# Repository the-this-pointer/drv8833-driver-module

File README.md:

### DRV8833 Stepper Motor Module

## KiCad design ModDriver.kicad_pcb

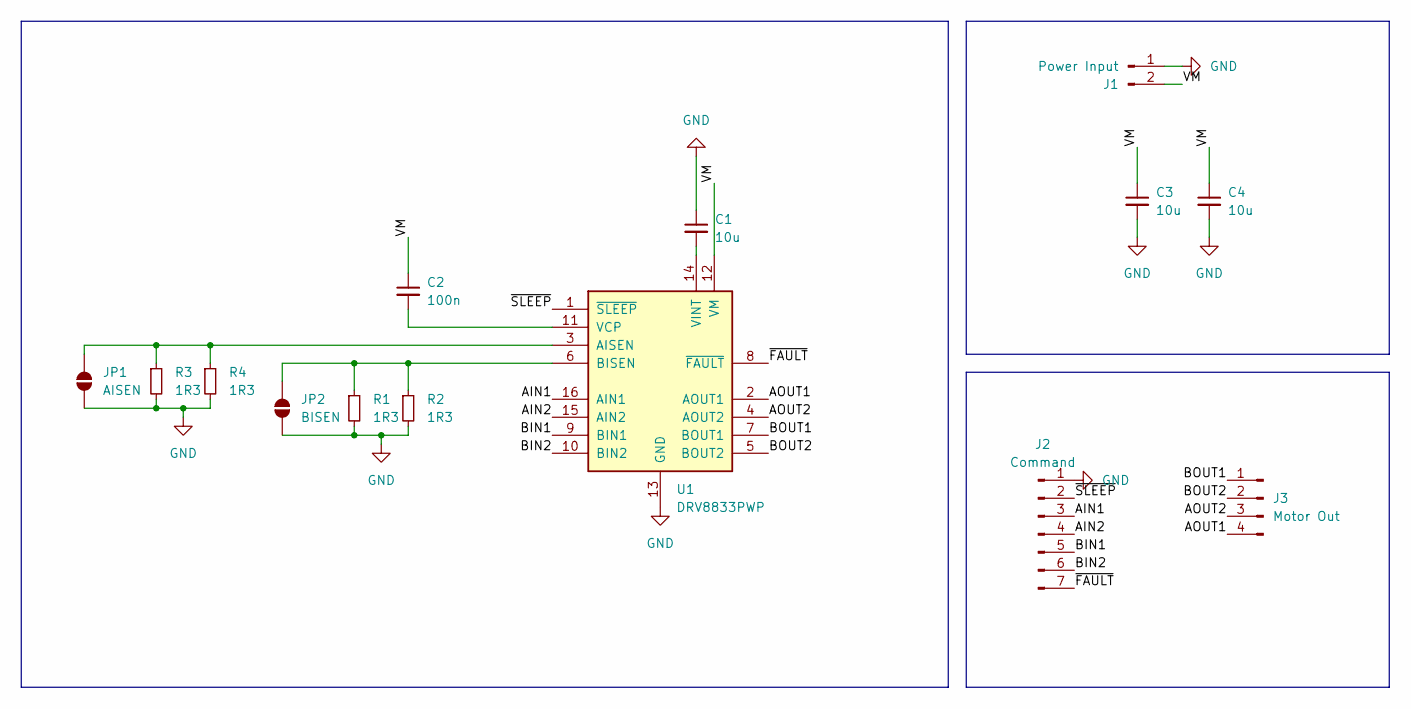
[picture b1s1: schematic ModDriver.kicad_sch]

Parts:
C1, C3, C4: 10u; C_1206_3216Metric_Pad1.33x1.80mm_HandSolder
C2: 100n; C_1206_3216Metric_Pad1.33x1.80mm_HandSolder
J1: Power Input; PinHeader_1x02_P2.54mm_Vertical
J2: Command; PinHeader_1x07_P2.54mm_Vertical
J3: Motor Out; PinHeader_1x04_P2.54mm_Vertical
JP1: AISEN; SolderJumper-2_P1.3mm_Open_TrianglePad1.0x1.5mm
JP2: BISEN; SolderJumper-2_P1.3mm_Open_TrianglePad1.0x1.5mm
R1, R2, R3, R4: 1R3; R_1206_3216Metric_Pad1.30x1.75mm_HandSolder
U1: DRV8833PWP; HTSSOP-16-1EP_4.4x5mm_P0.65mm_EP3.4x5mm_Mask2.46x2.31mm_The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

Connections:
/AIN1: J2.3, U1.16 (AIN1)
/AIN2: J2.4, U1.15 (AIN2)
/AOUT1: J3.4, U1.2 (AOUT1)
/AOUT2: J3.3, U1.4 (AOUT2)
/BIN1: J2.5, U1.9 (BIN1)
/BIN2: J2.6, U1.10 (BIN2)
/BOUT1: J3.1, U1.7 (BOUT1)
/BOUT2: J3.2, U1.5 (BOUT2)
/VM: C2.1, C3.1, C4.1, J1.2, U1.12 (VM)
/~FAULT: J2.7, U1.8 (~FAULT)
/~SLEEP: J2.2, U1.1 (~SLEEP)
GND: C1.1, C3.2, C4.2, J1.1, J2.1, JP1.2 (B), JP2.2 (B), R1.2, R2.2, R3.2, R4.2, U1.13 (GND), U1.17 (GND)
unnamed: JP1.1 (A), R3.1, R4.1, U1.3 (AISEN)
unnamed: JP2.1 (A), R1.1, R2.1, U1.6 (BISEN)
unnamed: C2.2, U1.11 (VCP)
unnamed: C1.2, U1.14 (VINT)

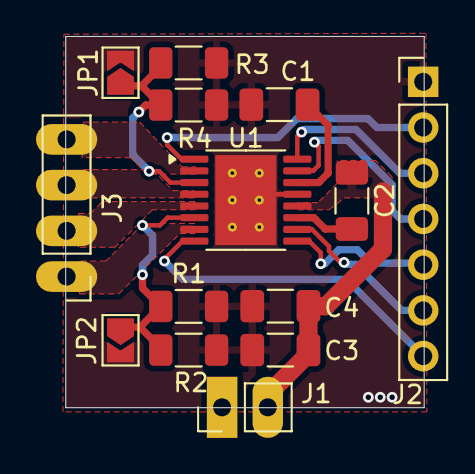
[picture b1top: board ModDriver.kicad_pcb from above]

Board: 2 copper layers, 19.9 x 20.6 mm, 14 parts (0 on the bottom side), 16 nets.
